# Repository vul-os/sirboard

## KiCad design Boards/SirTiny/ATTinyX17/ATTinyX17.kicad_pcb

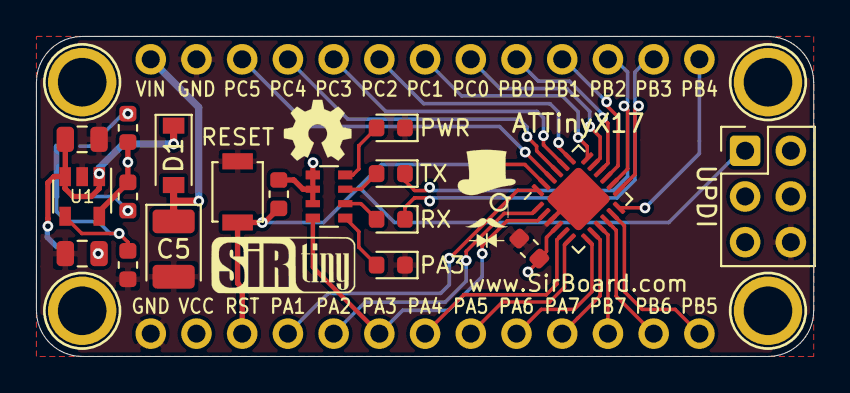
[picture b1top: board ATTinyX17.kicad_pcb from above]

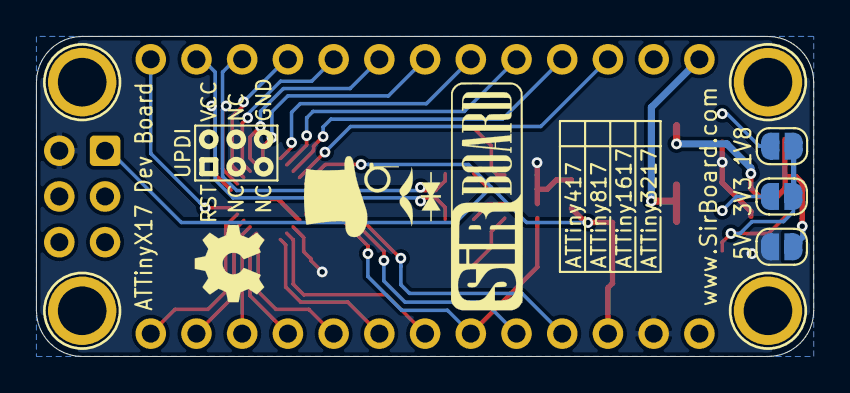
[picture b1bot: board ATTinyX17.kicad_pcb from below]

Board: 2 copper layers, 43.2 x 17.8 mm, 27 parts (5 on the bottom side), 33 nets.

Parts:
1V8, 3V3, 5V: SolderJumper_2_Open; SolderJumper-2_P1.3mm_Open_RoundedPad1.0x1.5mm
C1: 10uF; C_0805_2012Metric
C2: 2u2; C_0805_2012Metric
C3: 100nF; C_0603_1608Metric
C5: 22uF; CP_EIA-3528-15_AVX-H
D1: MBR120; D_SOD-123
H1, H2, H3, H4: MountingHole; MountingHole_M2.5_SirBoard
J1, J2: Conn_01x13; PinHeader_1x13_P2.54mm_Vertical
PA3: BLUE; LED_0603_1608Metric
PWR: RED; LED_0603_1608Metric
R3: 39k; R_0603_1608Metric
R4: 12.4k; R_0603_1608Metric
R5: 18k; R_0603_1608Metric
R6: 10k; R_0603_1608Metric
RESET: RST; SW_SPST_B3U-1000P
RN1: 330E; R_Array_Convex_4x0603
RX: YEL; LED_0603_1608Metric
TX: YEL; LED_0603_1608Metric
U1: AP7365; SOT-23-5
U2: ATtiny3217-M; QFN-24-1EP_4x4mm_P0.5mm_EP2.6x2.6mm
UPDI: UPDI; PinHeader_2x03_P2.54mm_Vertical

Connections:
/1V8: 1V8.2, R5.2
/3V3: 3V3.2, R3.2
/ADJ: 1V8.1, 3V3.1, R4.1, U1.4
GND: C1.2, C2.2, C3.2, C5.2, J1.1, J2.2, PA3.1, PWR.1, R4.2, RESET.2, U1.2, U2.3, U2.25, UPDI.6
unnamed: 5V.2, C1.1, D1.1, U1.1, U1.3
unnamed: PA3.2, RN1.1
unnamed: PWR.2, RN1.4
unnamed: RN1.2, RX.2
unnamed: RN1.3, TX.2
PA1: J1.4, U2.24
PA2: J1.5, U2.1
PA3: J1.6, RN1.8, U2.2
PA4: J1.7, U2.5
PA5: J1.8, U2.6
PA6: J1.9, U2.7
PA7: J1.10, U2.8
PB0: J2.9, U2.16
PB1: J2.10, U2.15
PB4: J2.13, U2.12
PB5: J1.13, U2.11
PB6: J1.12, U2.10
PB7: J1.11, U2.9
PC0: J2.8, U2.17
PC1: J2.7, U2.18
PC2: J2.6, U2.19
PC3: J2.5, U2.20
PC4: J2.4, U2.21
PC5: J2.3, U2.22
RST: J1.3, R6.2, RESET.1, U2.23, UPDI.1
RXD: J2.12, RX.1, U2.13
TXD: J2.11, TX.1, U2.14
VCC: 5V.1, C2.1, C3.1, J1.2, R3.1, R5.1, R6.1, RN1.5, RN1.6, RN1.7, U1.5, U2.4, UPDI.2
VIN: C5.1, D1.2, J2.1

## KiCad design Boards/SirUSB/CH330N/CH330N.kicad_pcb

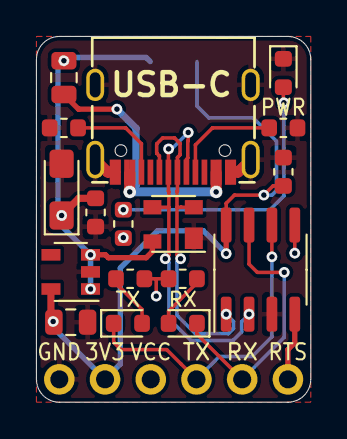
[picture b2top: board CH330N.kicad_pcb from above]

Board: 2 copper layers, 15.2 x 20.3 mm, 19 parts (1 on the bottom side), 15 nets.

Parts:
C1, C4: 100nF; C_0603_1608Metric
C3: 22uF; CP_EIA-3216-18_Kemet-A_Pad1.58x1.35mm_HandSolder
C7: 10uF; C_0805_2012Metric
D1: PRTR5V0U2X; SOT-143
F1: 500mA; R_0805_2012Metric
J2: Conn_01x06; PinHeader_1x06_P2.54mm_Horizontal
PWR: BLUE; LED_0603_1608Metric
R1, R2, R3: 1K; R_0603_1608Metric
R4, R5: 5K1; R_0603_1608Metric
RX1: GREEN; LED_0603_1608Metric
TX2: RED; LED_0603_1608Metric
U1: CH330N; SOIC-8_3.9x4.9mm_P1.27mm
U2: AP2127K-3.3; SOT-23-5
USB-C: USB_C_Plug_USB2.0; USB_C
VCC: SolderJumper_3_Open; SolderJumper-3_P1.3mm_Open_RoundedPad1.0x1.5mm

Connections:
3V3: C1.2, C7.1, J2.5, U1.8, U2.5, VCC.3
D+: D1.2, U1.1, USB-C.A6, USB-C.B6
D-: D1.3, U1.2, USB-C.A7, USB-C.B7
GND: C1.1, C3.2, C4.2, C7.2, D1.1, J2.6, PWR.1, R4.2, R5.2, U1.3, U2.2, USB-C.A1, USB-C.A12, USB-C.B1, USB-C.B12, USB-C.S1
unnamed: F1.2, USB-C.A4, USB-C.A9, USB-C.B4, USB-C.B9
unnamed: R5.1, USB-C.A5
unnamed: R4.1, USB-C.B5
unnamed: PWR.2, R1.2
unnamed: R2.2, TX2.2
unnamed: R3.2, RX1.2
RTS: J2.1, U1.4
RX: J2.2, RX1.1, U1.7
TX: J2.3, TX2.1, U1.6
VBUS: C3.1, C4.1, D1.4, F1.1, U2.1, U2.3, VCC.1
VCC: J2.4, R1.1, R2.1, R3.1, U1.5, VCC.2

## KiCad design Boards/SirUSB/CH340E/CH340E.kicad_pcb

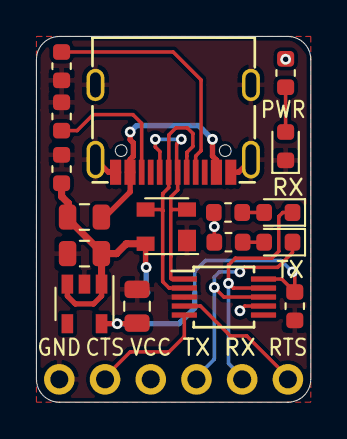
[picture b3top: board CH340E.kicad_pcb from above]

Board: 2 copper layers, 15.2 x 20.3 mm, 19 parts (1 on the bottom side), 16 nets.

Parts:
C1, C4: 100nF; C_0603_1608Metric
C6, C7: 10uF; C_0805_2012Metric
D1: PRTR5V0U2X; SOT-143
F1: 500mA; Fuse_0805_2012Metric
J2: Conn_01x06; PinHeader_1x06_P2.54mm_Horizontal
P1: USB_C_Plug_USB2.0; USB_C
PWR: RED; LED_0603_1608Metric
R1, R2, R3: 1K; R_0603_1608Metric
R4, R5: 5K1; R_0603_1608Metric
RX1: GREEN; LED_0603_1608Metric
TX1: GREEN; LED_0603_1608Metric
U1: CH340E; MSOP-10_3x3mm_P0.5mm
U2: AP2127K-3.3; SOT-23-5
VCC: SolderJumper_3_Open; SolderJumper-3_P1.3mm_Open_RoundedPad1.0x1.5mm

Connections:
3V3: C1.2, C7.1, U1.10, U2.5, VCC.3
CTS: J2.5, U1.5
D+: D1.2, P1.A6, P1.B6, U1.1
D-: D1.3, P1.A7, P1.B7, U1.2
GND: C1.1, C4.2, C6.2, C7.2, D1.1, J2.6, P1.A1, P1.A12, P1.B1, P1.B12, P1.S1, PWR.1, R4.2, R5.2, U1.3, U2.2
unnamed: F1.2, P1.A4, P1.A9, P1.B4, P1.B9
unnamed: P1.A5, R5.1
unnamed: P1.B5, R4.1
unnamed: PWR.2, R1.2
unnamed: R2.2, TX1.2
unnamed: R3.2, RX1.2
RTS: J2.1, U1.4
RX: J2.2, RX1.1, U1.9
TX: J2.3, TX1.1, U1.8
VBUS: C4.1, C6.1, D1.4, F1.1, U2.1, U2.3, VCC.1
VCC: J2.4, R1.1, R2.1, R3.1, U1.7, VCC.2

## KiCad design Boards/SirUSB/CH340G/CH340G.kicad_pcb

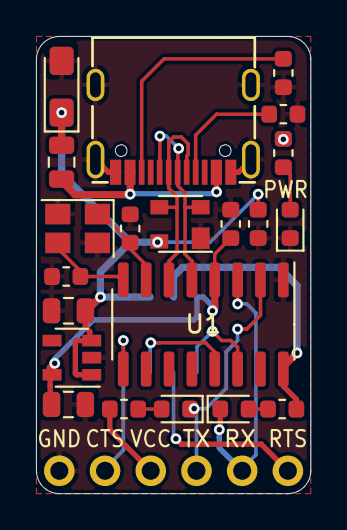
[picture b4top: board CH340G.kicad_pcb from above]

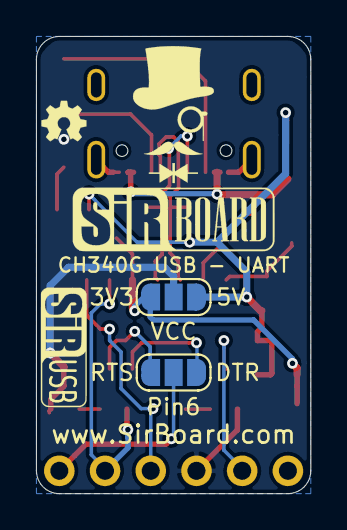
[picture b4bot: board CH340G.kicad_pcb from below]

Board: 2 copper layers, 15.2 x 25.4 mm, 24 parts (2 on the bottom side), 20 nets.

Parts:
C1, C2: 9pF; C_0603_1608Metric
C3: 22uF; CP_EIA-3216-18_Kemet-A_Pad1.58x1.35mm_HandSolder
C4: 100nF; C_0603_1608Metric
C5: 10nF; C_0603_1608Metric
C6, C7: 10uF; C_0805_2012Metric
D1: PRTR5V0U2X; SOT-143
F1: 500mA; R_0805_2012Metric
J2: Conn_01x06; PinHeader_1x06_P2.54mm_Horizontal
P1: USB_C_Plug_USB2.0; USB_C
PWR: BLUE; LED_0603_1608Metric
Pin6: SolderJumper_3_Open; SolderJumper-3_P1.3mm_Open_RoundedPad1.0x1.5mm
R1, R2, R3: 1K; R_0603_1608Metric
R4, R5: 5K1; R_0603_1608Metric
RX1: GREEN; LED_0603_1608Metric
TX2: RED; LED_0603_1608Metric
U1: CH340G; SOIC-16_3.9x9.9mm_P1.27mm
U2: AP2127K-3.3; SOT-23-5
VCC: SolderJumper_3_Open; SolderJumper-3_P1.3mm_Open_RoundedPad1.0x1.5mm
Y1: Crystal_GND24; Crystal_SMD_SeikoEpson_TSX3225-4Pin_3.2x2.5mm

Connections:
3V3: C5.2, C7.1, U1.4, U2.5, VCC.3
CTS: J2.5, U1.9
D+: D1.2, P1.A6, P1.B6, U1.5
D-: D1.3, P1.A7, P1.B7, U1.6
DTR: Pin6.1, U1.13
GND: C1.2, C2.2, C3.2, C4.2, C5.1, C6.2, C7.2, D1.1, J2.6, P1.A1, P1.A12, P1.B1, P1.B12, P1.S1, PWR.1, R4.2, R5.2, U1.1, U2.2, Y1.2, Y1.4
unnamed: C1.1, U1.7, Y1.1
unnamed: C2.1, U1.8, Y1.3
unnamed: F1.2, P1.A4, P1.A9, P1.B4, P1.B9
unnamed: P1.A5, R5.1
unnamed: P1.B5, R4.1
unnamed: PWR.2, R1.2
unnamed: R2.2, TX2.2
unnamed: R3.2, RX1.2
P6: J2.1, Pin6.2
RTS: Pin6.3, U1.14
RX: J2.2, RX1.1, U1.3
TX: J2.3, TX2.1, U1.2
VBUS: C3.1, C4.1, C6.1, D1.4, F1.1, U2.1, U2.3, VCC.1
VCC: J2.4, R1.1, R2.1, R3.1, U1.16, VCC.2

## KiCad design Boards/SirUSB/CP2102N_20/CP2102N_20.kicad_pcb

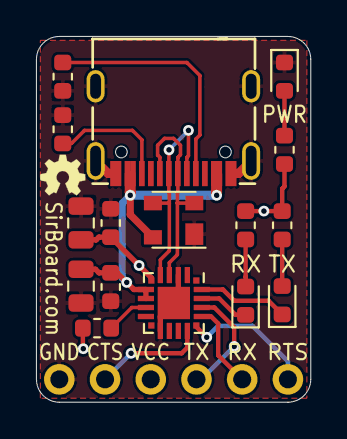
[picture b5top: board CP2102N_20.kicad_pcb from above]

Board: 2 copper layers, 15.2 x 20.3 mm, 17 parts (0 on the bottom side), 17 nets.

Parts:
C1, C4: 100nF; C_0603_1608Metric
C2, C5: 4.7uF; C_0805_2012Metric
D1: PRTR5V0U2X; SOT-143
J1: Conn_01x06; PinHeader_1x06_P2.54mm_Horizontal
P1: USB_C_Plug_USB2.0; USB_C
PWR: RED; LED_0603_1608Metric
R1, R3, R5, R6: 1K; R_0603_1608Metric
R2, R4: 5K1; R_0603_1608Metric
RX: GREEN; LED_0603_1608Metric
TX: GREEN; LED_0603_1608Metric
U1: CP2102N-A01-GQFN20; SiliconLabs_QFN-20-1EP_3x3mm_P0.5mm

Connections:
/CC1: P1.A5, R4.1
/CC2: P1.B5, R2.1
CTS: J1.5, U1.15
GND: C1.2, C2.2, C4.2, C5.2, D1.1, J1.6, P1.A1, P1.A12, P1.B1, P1.B12, P1.S1, PWR.1, R2.2, R4.2, U1.3, U1.12, U1.21
GPIO.2: TX.1, U1.20
GPIO.3: RX.1, U1.19
unnamed: PWR.2, R1.2
unnamed: R3.2, TX.2
unnamed: R5.2, RX.2
RST: R6.2, U1.9
RTS: J1.1, U1.16
RX: J1.2, U1.17
TX: J1.3, U1.18
VBUS: C1.1, C2.1, D1.4, P1.A4, P1.A9, P1.B4, P1.B9, U1.7, U1.8
VDD: C4.1, C5.1, J1.4, R1.1, R3.1, R5.1, R6.1, U1.6
uD+: D1.2, P1.A6, P1.B6, U1.4
uD-: D1.3, P1.A7, P1.B7, U1.5

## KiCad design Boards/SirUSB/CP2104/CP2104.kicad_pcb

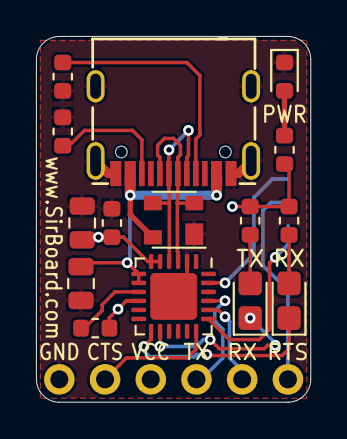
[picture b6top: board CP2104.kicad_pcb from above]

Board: 2 copper layers, 15.2 x 20.3 mm, 17 parts (1 on the bottom side), 19 nets.

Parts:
C1: 1uF; C_0805_2012Metric
C4: 100nF; C_0603_1608Metric
C5: 4.7uF; C_0805_2012Metric
D1: PRTR5V0U2X; SOT-143
J1: Conn_01x06; PinHeader_1x06_P2.54mm_Horizontal
JP2: SolderJumper_3_Open; SolderJumper-3_P1.3mm_Open_RoundedPad1.0x1.5mm
P1: USB_C_Plug_USB2.0; USB_C
PWR: RED; LED_0603_1608Metric
R1, R3, R5: 1K; R_0603_1608Metric
R2, R4: 5K1; R_0603_1608Metric
R6: 4K7; R_0603_1608Metric
RX: GREEN; LED_0805_2012Metric_Castellated
TX: GREEN; LED_0805_2012Metric_Castellated
U1: CP2104; QFN-24-1EP_4x4mm_P0.5mm_EP2.6x2.6mm

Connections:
/CC1: P1.A5, R4.1
/CC2: P1.B5, R2.1
CTS: J1.5, U1.18
DTR: JP2.3, U1.23
DTR_RTS: J1.1, JP2.2
GND: C1.2, C4.2, C5.2, D1.1, J1.6, P1.A1, P1.A12, P1.B1, P1.B12, P1.S1, PWR.1, R2.2, R4.2, U1.2, U1.25
GPIO.0: TX.1, U1.14
GPIO.1: RX.1, U1.13
unnamed: PWR.2, R1.2
unnamed: R3.2, TX.2
unnamed: R5.2, RX.2
RST: R6.2, U1.9
RTS: JP2.1, U1.19
RX: J1.2, U1.20
TX: J1.3, U1.21
VBUS: C1.1, D1.4, P1.A4, P1.A9, P1.B4, P1.B9, U1.7, U1.8
VDD: C4.1, C5.1, J1.4, R1.1, R3.1, R5.1, R6.1, U1.5, U1.6, U1.10
uD+: D1.2, P1.A6, P1.B6, U1.3
uD-: D1.3, P1.A7, P1.B7, U1.4

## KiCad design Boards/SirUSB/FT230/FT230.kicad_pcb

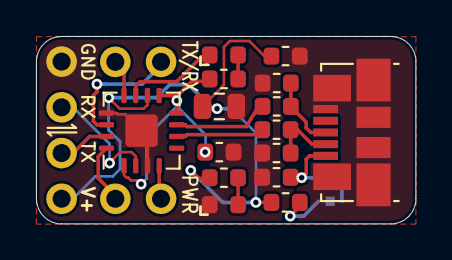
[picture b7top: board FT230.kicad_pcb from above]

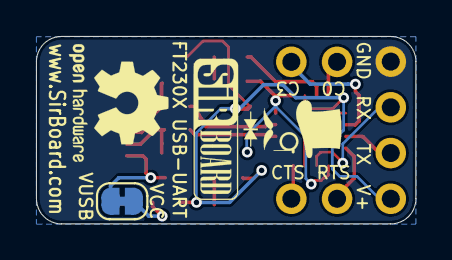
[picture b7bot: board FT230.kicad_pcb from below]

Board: 2 copper layers, 21.1 x 10.4 mm, 19 parts (2 on the bottom side), 18 nets.

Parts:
C1: 10nF; C_0603_1608Metric
C2, C3: 47pF; C_0603_1608Metric
C4, C6: 100nF; C_0603_1608Metric
C5: 4.7uF; C_0805_2012Metric
FB1: Ferrite_Bead; L_0603_1608Metric
J1: USB_B_Micro; USB_Micro-B_Molex_47346-0001
J2: Conn_01x04; PinHeader_1x04_P2.54mm_Vertical
J3, J4: Conn_01x02; PinHeader_1x02_P2.54mm_Vertical
JP1: SolderJumper_2_Open; SolderJumper-2_P1.3mm_Bridged_RoundedPad1.0x1.5mm
PWR: PWR; LED_0603_1608Metric
R1, R2: 27e; R_0603_1608Metric
R3: 270E; R_0603_1608Metric
R4: 1K; R_0603_1608Metric
TX/RX: RX; LED_0603_1608Metric
U1: FT230XQ; QFN-16-1EP_4x4mm_P0.65mm_EP2.1x2.1mm

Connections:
/3.3V: C6.1, R3.1, U1.1, U1.8, U1.9
/D+: C2.1, J1.3, R1.1
/D-: C3.1, J1.2, R2.2
/RX: J2.3, U1.2
/TX: J2.2, U1.15
/VCC: C4.1, C5.1, FB1.1, J2.1, R4.1, U1.10
/VUSB: C1.1, J1.1, JP1.1
/uD+: R1.2, U1.7
/uD-: R2.1, U1.6
GND: C1.2, C2.2, C3.2, C4.2, C5.2, C6.2, J1.5, J1.6, J2.4, PWR.1, U1.3, U1.13, U1.17
unnamed: FB1.2, JP1.2
unnamed: J3.1, U1.16
unnamed: J3.2, U1.4
unnamed: J4.1, U1.12
unnamed: J4.2, U1.14
unnamed: PWR.2, R4.2
unnamed: R3.2, TX/RX.2
unnamed: TX/RX.1, U1.11

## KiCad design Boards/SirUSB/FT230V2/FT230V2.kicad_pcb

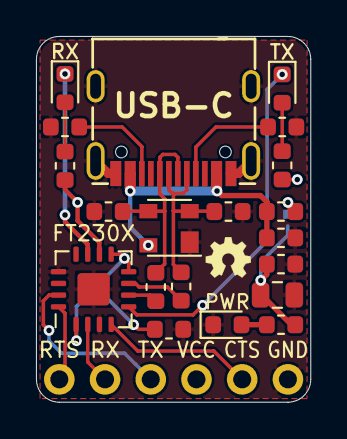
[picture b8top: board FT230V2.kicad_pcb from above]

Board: 2 copper layers, 15.2 x 20.3 mm, 22 parts (1 on the bottom side), 20 nets.

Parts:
C1: 10nF; C_0603_1608Metric
C2, C3: 47pF; C_0603_1608Metric
C4, C6: 100nF; C_0603_1608Metric
C5: 4.7uF; C_0805_2012Metric
D1: PRTR5V0U2X; SOT-143
FB1: 40E@100MHz; L_0603_1608Metric
J1: Conn_01x06; PinHeader_1x06_P2.54mm_Horizontal
JP1: SolderJumper_2_Open; SolderJumper-2_P1.3mm_Bridged_RoundedPad1.0x1.5mm
PWR: RED; LED_0603_1608Metric
R1, R2: 27e; R_0603_1608Metric
R3, R4, R5: 1k; R_0603_1608Metric
R6, R7: 5k1; R_0603_1608Metric
RX: GREEN; LED_0603_1608Metric
TX: GREEN; LED_0603_1608Metric
U1: FT230XQ; QFN-16-1EP_4x4mm_P0.65mm_EP2.1x2.1mm
USB-C: USB_C_Plug_USB2.0; USB_C

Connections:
CBUS1: RX.1, U1.11
CBUS2: TX.1, U1.5
CTS: J1.2, U1.4
D+: C2.1, D1.3, R2.2, USB-C.A6, USB-C.B6
D-: C3.1, D1.2, R1.1, USB-C.A7, USB-C.B7
GND: C1.2, C2.2, C3.2, C4.2, C5.2, C6.2, D1.1, J1.1, PWR.1, R6.2, R7.2, U1.3, U1.13, U1.17, USB-C.A1, USB-C.A12, USB-C.B1, USB-C.B12, USB-C.S1
unnamed: C6.1, U1.1, U1.8, U1.9
unnamed: FB1.1, JP1.1
unnamed: R7.1, USB-C.A5
unnamed: R6.1, USB-C.B5
unnamed: PWR.2, R4.2
unnamed: R3.2, TX.2
unnamed: R5.2, RX.2
RTS: J1.6, U1.16
RX: J1.5, U1.2
TX: J1.4, U1.15
VCC: C4.1, C5.1, J1.3, JP1.2, R3.1, R4.1, R5.1, U1.10
VUSB: C1.1, D1.4, FB1.2, USB-C.A4, USB-C.A9, USB-C.B4, USB-C.B9
uD+: R2.1, U1.6
uD-: R1.2, U1.7
